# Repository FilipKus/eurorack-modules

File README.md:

# eurorack-modules

This repo is a collection of eurorack modules designed on KiCad 7.0 currently containing the following modules:

VCA: 2-channel voltage-controlled amplifier (VCA)

ADSR Envelope Generator: 1-channel attack, decay, sustain and release envelope generator with one input and one output.

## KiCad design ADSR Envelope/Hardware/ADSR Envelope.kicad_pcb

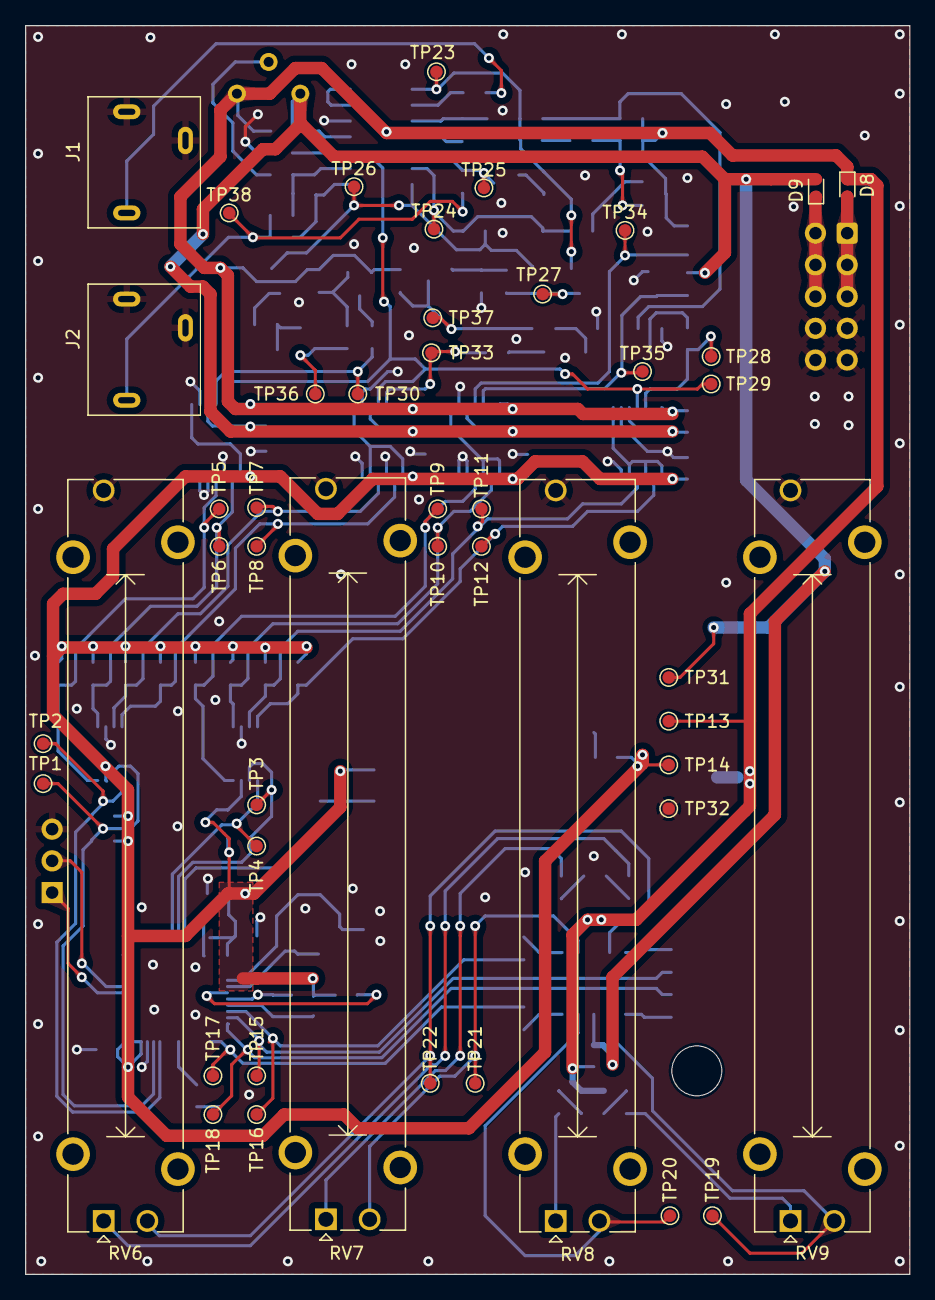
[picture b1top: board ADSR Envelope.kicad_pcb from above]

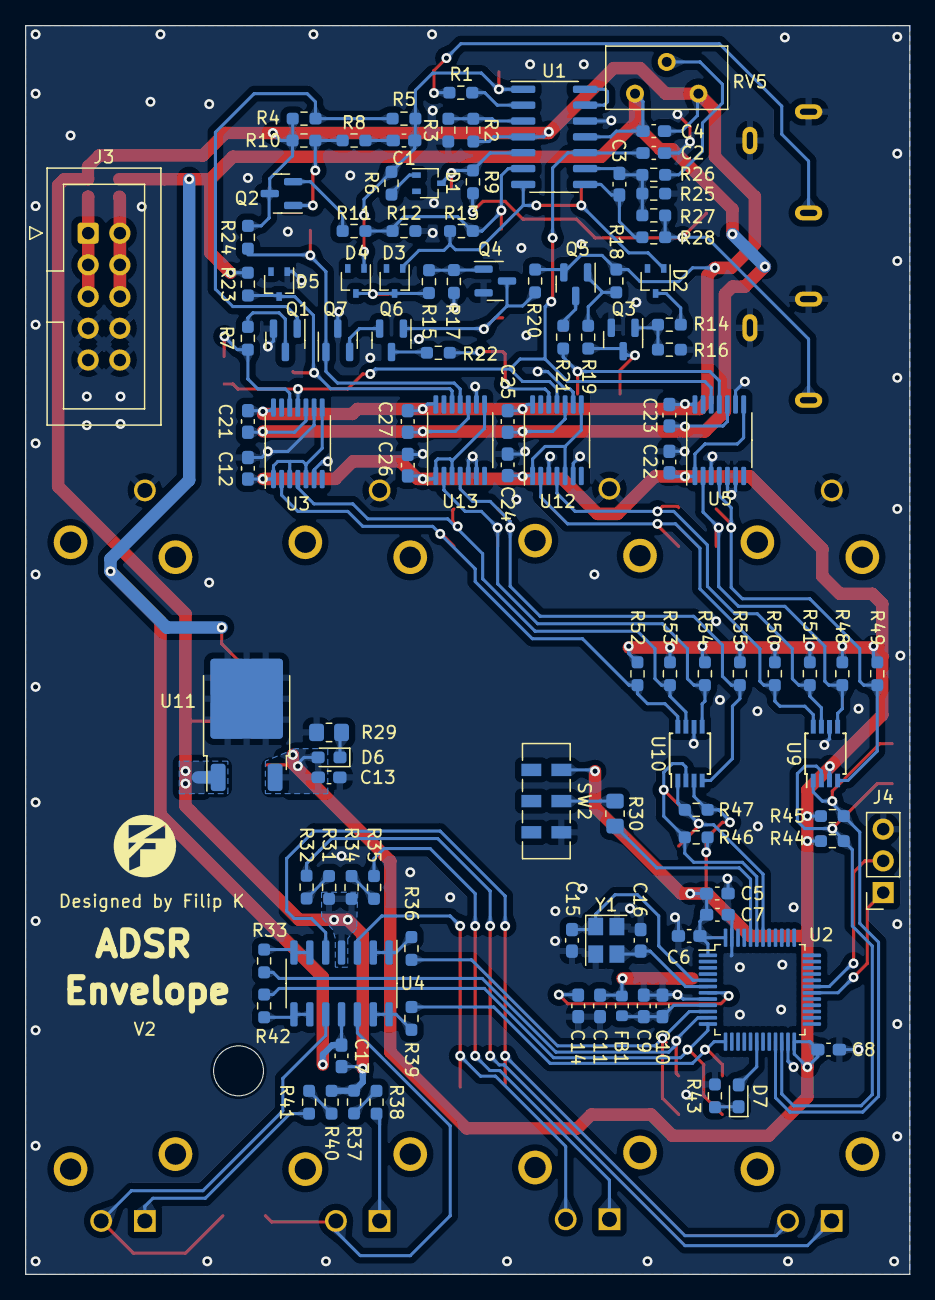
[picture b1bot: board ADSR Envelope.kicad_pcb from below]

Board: 2 copper layers, 70.8 x 100.0 mm, 155 parts (109 on the bottom side), 83 nets.

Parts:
C1, C9: 10n; C_0603_1608Metric_Pad1.08x0.95mm_HandSolder
C2: 2.2uF; C_0603_1608Metric_Pad1.08x0.95mm_HandSolder
C3: 47pF; C_0603_1608Metric_Pad1.08x0.95mm_HandSolder
C4, C17: 100nF; C_0603_1608Metric_Pad1.08x0.95mm_HandSolder
C5: 10u; C_0603_1608Metric_Pad1.08x0.95mm_HandSolder
C6, C7, C8, C12, C14, C21, C22, C23, C24, C25, C26, C27: 100n; C_0603_1608Metric_Pad1.08x0.95mm_HandSolder
C10, C11, C13: 1u; C_0603_1608Metric_Pad1.08x0.95mm_HandSolder
C15, C16: 10p; C_0603_1608Metric_Pad1.08x0.95mm_HandSolder
D1, D2, D3, D4, D5: BAS16W; SOT-323_SC-70
D6, D7: RED LED; LED_0603_1608Metric_Pad1.05x0.95mm_HandSolder
D8, D9: BAS516; D_SOD-523
FB1: FerriteBead; L_0603_1608Metric
J1, J2: AudioJack2_SwitchT; Jack_3.5mm_VCO
J3: Conn_02x05_Odd_Even; IDC-Header_2x05_P2.54mm_Vertical
J4: Conn_01x03_Socket; PinSocket_1x03_P2.54mm_Vertical
Q1, Q3, Q4, Q6: BC847; SOT-23
Q2, Q5, Q7: BC857; SOT-23
R1, R4, R5, R6, R7, R8, R11, R14, R15, R16, R17, R18, R19, R20, R23, R27, R32, R33, R35, R36, R38, R39, R41, R42: 10K; R_0603_1608Metric_Pad0.98x0.95mm_HandSolder
R2, R9, R10, R25, R26: 100K; R_0603_1608Metric_Pad0.98x0.95mm_HandSolder
R3: 15K; R_0603_1608Metric_Pad0.98x0.95mm_HandSolder
R12: 62K; R_0603_1608Metric_Pad0.98x0.95mm_HandSolder
R13: 75K; R_0603_1608Metric_Pad0.98x0.95mm_HandSolder
R21: 4.7K; R_0603_1608Metric_Pad0.98x0.95mm_HandSolder
R22, R44, R45, R46, R47, R48, R49, R50, R51, R52, R53, R54, R55: 1K; R_0603_1608Metric_Pad0.98x0.95mm_HandSolder
R24: 270K; R_0603_1608Metric_Pad0.98x0.95mm_HandSolder
R28: 330R; R_0603_1608Metric_Pad0.98x0.95mm_HandSolder
R29: 1K5; R_0805_2012Metric_Pad1.20x1.40mm_HandSolder
R30: 10K; R_0805_2012Metric_Pad1.20x1.40mm_HandSolder
R31, R34, R37, R40: 18K; R_0603_1608Metric_Pad0.98x0.95mm_HandSolder
R43: 1K5; R_0603_1608Metric_Pad0.98x0.95mm_HandSolder
RV5: R_Potentiometer; Potentiometer_Bourns_3296Y_Vertical
RV6, RV7, RV8, RV9: 10K; Potentiometer_Bourns_PTA4543_Single_Slide
SW2: SW_DPDT_x2; SW_DPDT_CK_JS202011JCQN
TP1, TP2, TP3, TP4, TP5, TP6, TP7, TP8, TP9, TP10, TP11, TP12, TP13, TP14, TP15, TP16, TP17, TP18, TP19, TP20, TP21, TP22, TP23, TP24, TP25, TP26, TP27, TP28, TP29, TP30, TP31, TP32, TP33, TP34, TP35, TP36, TP37, TP38: TestPoint; TestPoint_Pad_D1.0mm
U1, U4: TL074; SOIC-14_3.9x8.7mm_P1.27mm
U2: STM32F030C8Tx; LQFP-48_7x7mm_P0.5mm
U3, U5, U12, U13: MCP45HV31-ST; TSSOP-14_4.4x5mm_P0.65mm
U9, U10: TSSOP-8_3x3mm_P0.65mm
U11: LP2950-3.3_TO252; TO-252-2
Y1: 16MHz; Crystal_SMD_3225-4Pin_3.2x2.5mm

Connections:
+3.3V: C5.1, C6.1, C7.1, C8.1, C11.1, C12.2, C13.1, C22.2, C24.2, C26.2, D6.2 (A), FB1.2, R44.2, R45.2, R46.2, R47.2, R48.2, R49.2, R50.2, R51.2, R52.2, R53.2, R54.2, R55.2, SW2.1 (A), TP14.1, U2.1 (VDD), U2.24 (VDD), U2.48 (VDD), U3.1 (VL), U3.3 (A1), U3.5 (A0), U3.8 (~SHDN), U5.1 (VL), U5.8 (~SHDN), U9.3 (VDD), U10.3 (VDD), U11.3 (VO), U12.1 (VL), U12.5 (A0), U12.8 (~SHDN), U13.1 (VL), U13.3 (A1), U13.8 (~SHDN)
+3.3VA: C9.1, C10.1, FB1.1, U2.9 (VDDA)
+12V: C4.1, C17.1, C21.2, C23.2, C25.2, C27.2, D8.1 (K), Q2.3 (C), Q5.2 (E), R2.2, R4.2, R10.2, R18.1, R20.1, R24.1, R31.1, R34.1, R37.1, R40.1, RV5.3, TP13.1, U1.4 (V+), U3.14 (V+), U4.4 (V+), U5.14 (V+), U11.1 (VI), U12.14 (V+), U13.14 (V+)
-12V: C4.2, C17.2, C21.1, C23.1, C25.1, C27.1, D9.2 (A), R23.2, RV5.1, TP31.1, U1.11 (V-), U3.10 (V-), U4.11 (V-), U5.10 (V-), U12.10 (V-), U13.10 (V-)
/Analog/ATTACK_B: R21.2, TP30.1, U5.11 (P0B)
/Analog/DECAY_W: R22.1, TP33.1, U12.12 (P0W)
/Analog/DETECT: C1.1, D4.1 (A), R5.1, R6.2, TP23.1, U1.1
/Analog/Envelope: C2.2, TP29.1, U1.10 (+), U3.11 (P0B), U5.12 (P0W), U12.11 (P0B)
/Analog/GATE: J1.T, R1.2
/Analog/OUT: J2.T, R9.1, R27.2, R28.2, TP38.1
/Analog/RELEASE_W: R7.2, TP28.1, U3.12 (P0W)
/Analog/SUSTAIN_B: Q7.1 (B), R24.2, TP34.1, U13.11 (P0B)
/Analog/SUSTAIN_W: D5.3 (K), R23.1, TP35.1, U13.12 (P0W)
/Microcontroller/ADC_ATTACK: R33.2, TP15.1, U2.11 (PA1)
/Microcontroller/ADC_DECAY: R36.2, TP16.1, U2.10 (PA0)
/Microcontroller/ADC_RELEASE: R42.2, TP18.1, U2.12 (PA2)
/Microcontroller/ADC_SUSTAIN: R39.2, TP17.1, U2.13 (PA3)
/Microcontroller/BOOT0: R30.2, U2.44 (BOOT0)
/Microcontroller/I2C1_SCL: R47.1, TP4.1, U2.42 (PB6), U10.1 (SCL)
/Microcontroller/I2C1_SDA: R46.1, TP3.1, U2.43 (PB7), U10.2 (SDA)
/Microcontroller/I2C2_SCL: R45.1, TP2.1, U2.21 (PB10), U9.1 (SCL)
/Microcontroller/I2C2_SDA: R44.1, TP1.1, U2.22 (PB11), U9.2 (SDA)
/Microcontroller/OSC_IN: C15.1, U2.5 (PF0), Y1.1
/Microcontroller/OSC_OUT: C16.1, U2.6 (PF1), Y1.3
/Microcontroller/PWR_LED_K: D6.1 (K), R29.2
/Microcontroller/SW_BOOT0: R30.1, SW2.2 (B)
/Microcontroller/USART1_RX: J4.2, U2.31 (PA10)
/Microcontroller/USART1_TX: J4.1, U2.30 (PA9)
ATTACK_SCL: R48.1, TP6.1, U5.2 (SCL), U9.5 (SC0)
ATTACK_SDA: R49.1, TP5.1, U5.4 (SDA), U9.4 (SD0)
DECAY_SCL: R50.1, TP8.1, U9.8 (SC1), U12.2 (SCL)
DECAY_SDA: R51.1, TP7.1, U9.7 (SD1), U12.4 (SDA)
GND: C2.1, C5.2, C6.2, C7.2, C8.2, C9.2, C10.2, C11.2, C12.1, C13.2, C14.1, C15.2, C16.2, C22.1, C24.1, C26.1, D5.1 (A), J1.S, J1.TN, J2.S, J2.TN, J3.7, J3.8, J3.9, J3.10, J4.3, Q1.2 (E), Q3.2 (E), Q4.2 (E), Q7.3 (C), R3.1, R12.2, R16.2, R17.2, R25.2, R29.1, R43.2, RV6.3, RV7.3, RV8.3, RV9.3, SW2.3 (C), TP32.1, U1.12 (+), U2.8 (VSSA), U2.23 (VSS), U2.47 (VSS), U3.6 (~WLAT), U3.9 (DGND), U5.3 (A1), U5.5 (A0), U5.6 (~WLAT), U5.9 (DGND), U9.6 (VSS), U10.6 (VSS), U11.2 (GND), U12.3 (A1), U12.6 (~WLAT), U12.9 (DGND), U13.5 (A0), U13.6 (~WLAT), U13.9 (DGND), Y1.2, Y1.4
unnamed: C1.2, R8.2
unnamed: C3.1, R28.1, U1.8
unnamed: D1.1 (A), R6.1
unnamed: D1.3 (K), R9.2, TP25.1, U1.5 (+)
unnamed: D2.1 (A), D3.1 (A), R13.1, TP26.1, U1.7
unnamed: D2.3 (K), R14.2
unnamed: D3.3 (K), D4.3 (K), R15.2, TP27.1
unnamed: D7.2 (A), U2.18 (PB0)
unnamed: D7.1 (K), R43.1
unnamed: D8.2 (A), J3.1, J3.3, J3.5
unnamed: D9.1 (K), J3.2, J3.4, J3.6
unnamed: Q1.1 (B), R4.1, R5.2
unnamed: Q1.3 (C), R7.1
unnamed: Q2.1 (B), R8.1, R10.1
unnamed: Q2.2 (E), R11.1
unnamed: Q3.1 (B), R14.1, R16.1
unnamed: Q3.3 (C), R19.2, TP36.1
unnamed: Q4.1 (B), R15.1, R17.1
unnamed: Q4.3 (C), Q6.1 (B), R20.2, TP37.1
unnamed: Q5.1 (B), R18.2, R19.1
unnamed: Q5.3 (C), R21.1
unnamed: Q6.3 (C), R22.2
unnamed: Q6.2 (E), Q7.2 (E)
unnamed: R26.2, RV5.2
unnamed: R31.2, R32.1
unnamed: R32.2, RV6.1
unnamed: R34.2, R35.1
unnamed: R35.2, RV7.1
unnamed: R37.2, R38.1
unnamed: R38.2, RV8.1
unnamed: R40.2, R41.1
unnamed: R41.2, RV9.1
unnamed: R2.1, R3.2, U1.3 (+)
unnamed: R1.1, U1.2 (-)
unnamed: R11.2, R12.1, R13.2, TP24.1, U1.6 (-)
unnamed: C3.2, R25.1, R26.1, R27.1, U1.9 (-)
unnamed: U1.13 (-), U1.14
unnamed: C14.2, U2.7 (NRST)
unnamed: RV7.2, TP21.1, U4.3 (+)
unnamed: R36.1, U4.1, U4.2 (-)
unnamed: RV6.2, TP22.1, U4.5 (+)
unnamed: R33.1, U4.6 (-), U4.7
unnamed: RV9.2, TP19.1, U4.10 (+)
unnamed: R42.1, U4.8, U4.9 (-)
unnamed: RV8.2, TP20.1, U4.12 (+)
unnamed: R39.1, U4.13 (-), U4.14
RELEASE_SCL: R52.1, TP12.1, U3.2 (SCL), U10.8 (SC1)
RELEASE_SDA: R53.1, TP11.1, U3.4 (SDA), U10.7 (SD1)
SUSTAIN_SCL: R54.1, TP10.1, U10.5 (SC0), U13.2 (SCL)
SUSTAIN_SDA: R55.1, TP9.1, U10.4 (SD0), U13.4 (SDA)

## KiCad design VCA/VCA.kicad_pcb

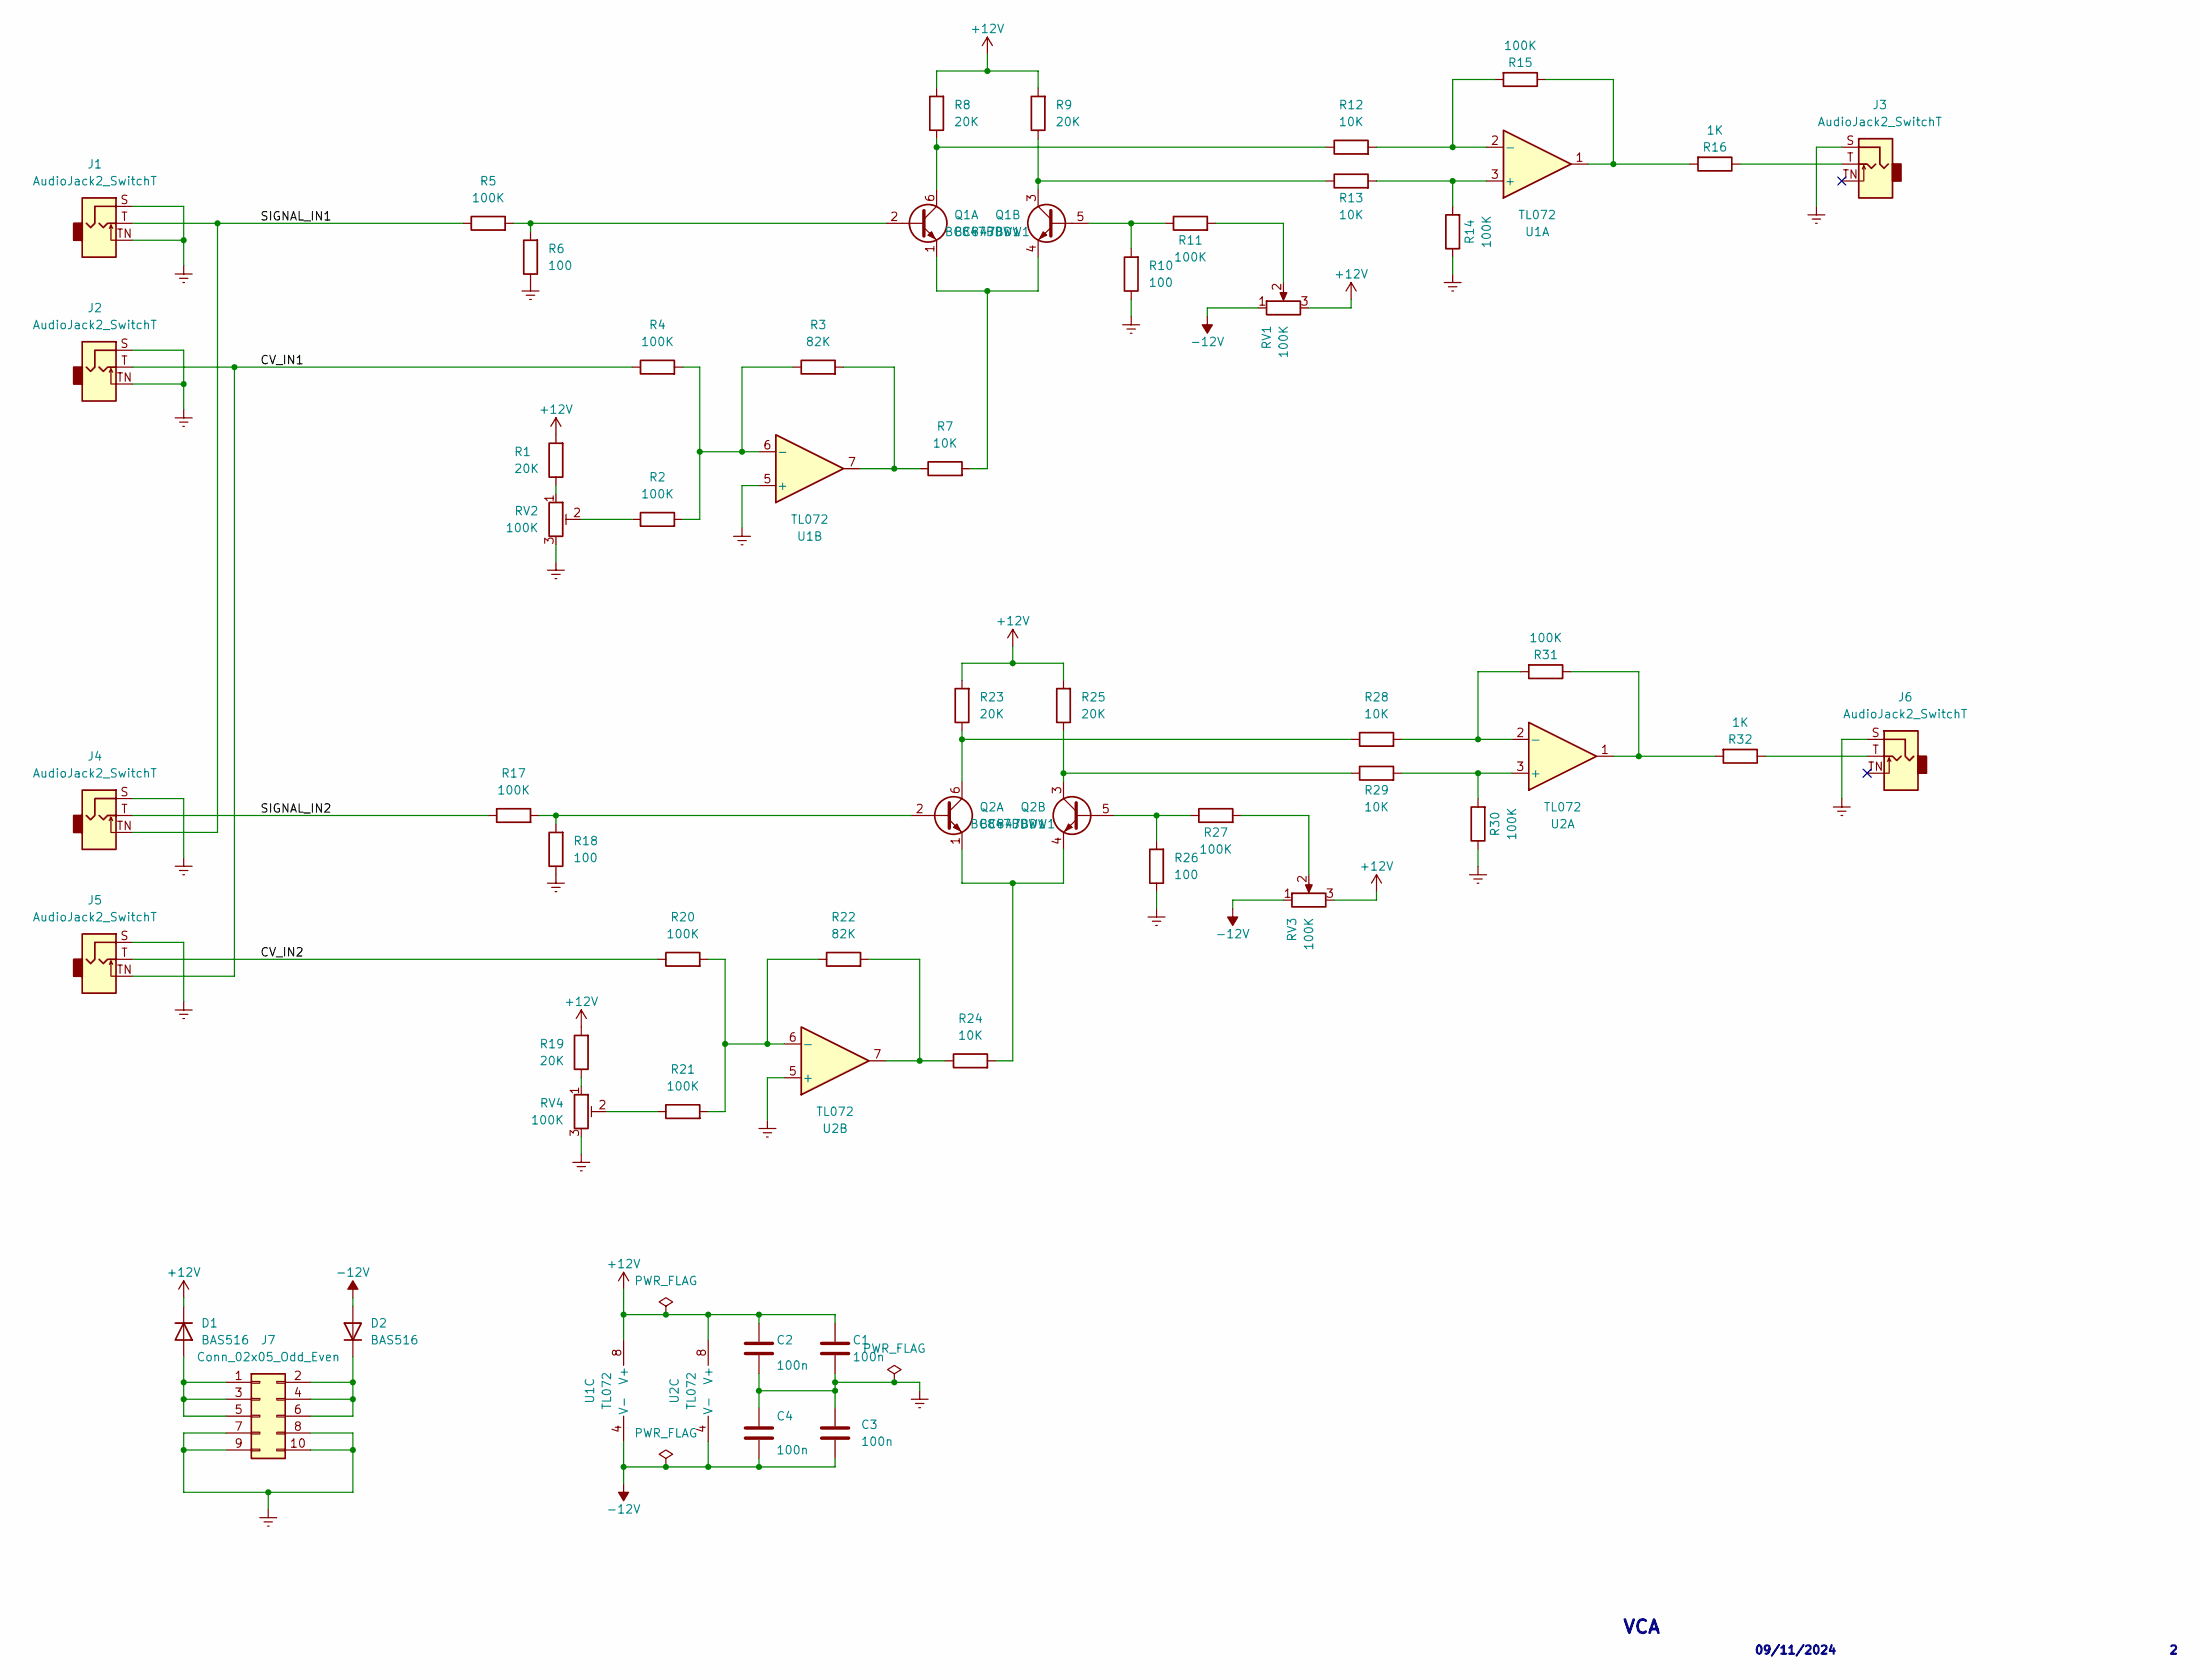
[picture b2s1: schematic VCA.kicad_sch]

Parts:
C1, C2, C3, C4: 100n; C_0603_1608Metric_Pad1.08x0.95mm_HandSolder
D1, D2: BAS516; D_SOD-523
J1, J2, J3, J4, J5, J6: AudioJack2_SwitchT; Jack_3.5mm_VCO
J7: Conn_02x05_Odd_Even; IDC-Header_2x05_P2.54mm_Vertical
Q1, Q2: BC847BDW1; SOT-363_SC-70-6
R1, R8, R9, R19, R23, R25: 20K; R_0603_1608Metric_Pad0.98x0.95mm_HandSolder
R2, R4, R5, R11, R14, R15, R17, R20, R21, R27, R30, R31: 100K; R_0603_1608Metric_Pad0.98x0.95mm_HandSolder
R3, R22: 82K; R_0603_1608Metric_Pad0.98x0.95mm_HandSolder
R6, R10, R18, R26: 100; R_0603_1608Metric_Pad0.98x0.95mm_HandSolder
R7, R12, R13, R24, R28, R29: 10K; R_0603_1608Metric_Pad0.98x0.95mm_HandSolder
R16, R32: 1K; R_0603_1608Metric_Pad0.98x0.95mm_HandSolder
RV1, RV3: 100K; Potentiometer_Bourns_3266W_Vertical
RV2, RV4: 100K; Potentiometer_Bourns_PTV09A-1_Single_Vertical
U1, U2: TL072; SOIC-8-1EP_3.9x4.9mm_P1.27mm_EP2.29x3mm

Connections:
+12V: C1.1, C2.1, D1.1 (K), R1.2, R8.2, R9.2, R19.2, R23.2, R25.2, RV1.3, RV3.3, U1.8 (V+), U2.8 (V+)
-12V: C3.2, C4.2, D2.2 (A), RV1.1, RV3.1, U1.4 (V-), U2.4 (V-)
/CV_IN1: J2.T, J5.TN, R4.1
/CV_IN2: J5.T, R20.1
/SIGNAL_IN1: J1.T, J4.TN, R5.1
/SIGNAL_IN2: J4.T, R17.1
GNDREF: C1.2, C2.2, C3.1, C4.1, J1.S, J1.TN, J2.S, J2.TN, J3.S, J4.S, J5.S, J6.S, J7.7, J7.8, J7.9, J7.10, R6.1, R10.1, R14.1, R18.1, R26.1, R30.1, RV2.3, RV4.3, U1.5 (+), U2.5 (+)
unnamed: D1.2 (A), J7.1, J7.3, J7.5
unnamed: D2.1 (K), J7.2, J7.4, J7.6
unnamed: J3.T, R16.1
unnamed: J6.T, R32.1
unnamed: Q1.2 (B1), R5.2, R6.2
unnamed: Q1.6 (C1), R8.1, R12.1
unnamed: Q1.1 (E1), Q1.4 (E2), R7.2
unnamed: Q1.5 (B2), R10.2, R11.1
unnamed: Q1.3 (C2), R9.1, R13.1
unnamed: Q2.2 (B1), R17.2, R18.2
unnamed: Q2.6 (C1), R23.1, R28.1
unnamed: Q2.1 (E1), Q2.4 (E2), R24.2
unnamed: Q2.5 (B2), R26.2, R27.1
unnamed: Q2.3 (C2), R25.1, R29.1
unnamed: R1.1, RV2.1
unnamed: R2.1, RV2.2
unnamed: R3.2, R7.1, U1.7
unnamed: R11.2, RV1.2
unnamed: R15.1, R16.2, U1.1
unnamed: R19.1, RV4.1
unnamed: R21.1, RV4.2
unnamed: R22.2, R24.1, U2.7
unnamed: R27.2, RV3.2
unnamed: R31.1, R32.2, U2.1
unnamed: R13.2, R14.2, U1.3 (+)
unnamed: R12.2, R15.2, U1.2 (-)
unnamed: R2.2, R3.1, R4.2, U1.6 (-)
unnamed: R29.2, R30.2, U2.3 (+)
unnamed: R28.2, R31.2, U2.2 (-)
unnamed: R20.2, R21.2, R22.1, U2.6 (-)

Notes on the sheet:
VCA
09/11/2024

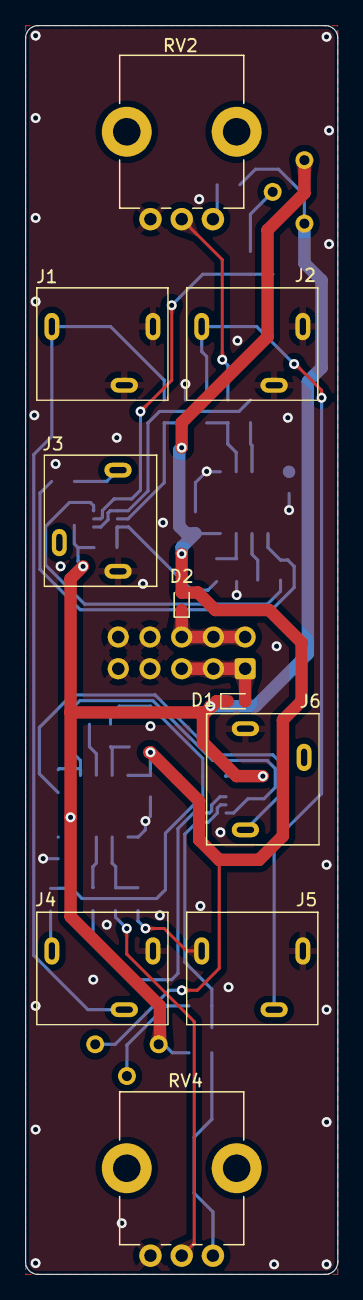
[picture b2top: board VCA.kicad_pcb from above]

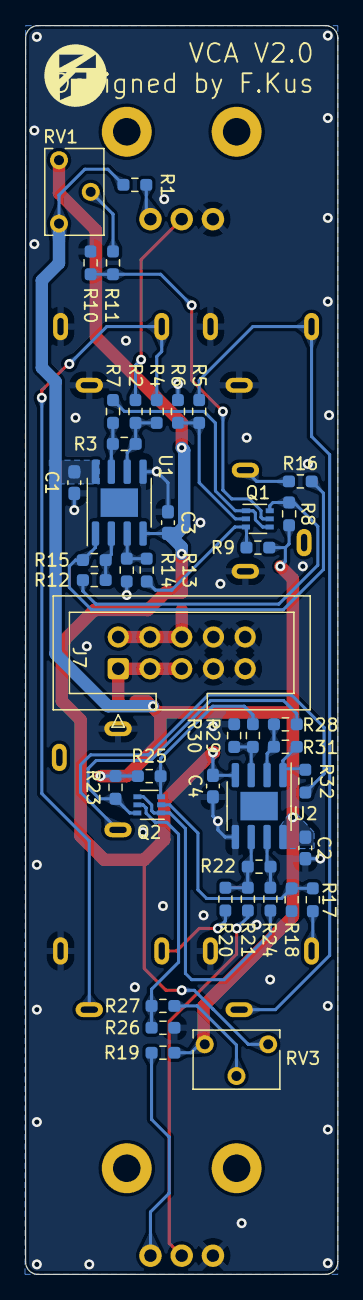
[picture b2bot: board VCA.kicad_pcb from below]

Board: 2 copper layers, 25.0 x 100.0 mm, 53 parts (43 on the bottom side), 37 nets.

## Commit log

2025-05-11 Adding the ADSR Envelope and VCA KiCad projects into the repo.
2025-05-11 Editing README.md to describe the two current modules a bit better
2025-05-11 Fixing small appearance bug in README.md
2025-07-14 Adding hardware and firmware folders in the ADSR Envelope folder
2025-07-14 Committing initial rust project which will be used to flash the STM32.
2025-07-14 Cleaning up code
    Adding comments. Updating print function to take in 'serial' variable and not 'tx' variable. Still need to create simple function for toggling LED on and off.
2025-07-15 Created a 'draw_line" function
    The draw_line function will draw a horizontal or vertical line on the terminal emulator. This will be used to draw volume bar looking objects for the attack, decay, sustain and release controls of th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
2025-07-16 Adding functions to draw level bars for the potentiometers
2025-07-17 Cleaning up other functions to make use of print_at_location functions
2025-07-17 Introduced 'Bar' struct in order to create and update bars easier and in a cleaner way
